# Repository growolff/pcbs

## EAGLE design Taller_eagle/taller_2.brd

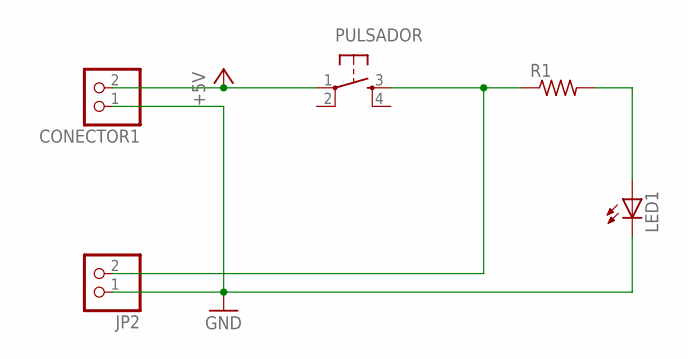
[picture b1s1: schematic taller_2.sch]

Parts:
CONECTOR1: PINHD-1X2/90; 1X02/90
JP2: PINHD-1X2/90; 1X02/90
LED1: LED5MM
PULSADOR: TAC_SWITCHPTH; TACTILE-PTH
R1: R-US_0207/12; 0207/12

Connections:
+5V: CONECTOR1.2, PULSADOR.1
GND: CONECTOR1.1, JP2.1, LED1.K (C)
unnamed: LED1.A, R1.2
unnamed: JP2.2, PULSADOR.3, R1.1

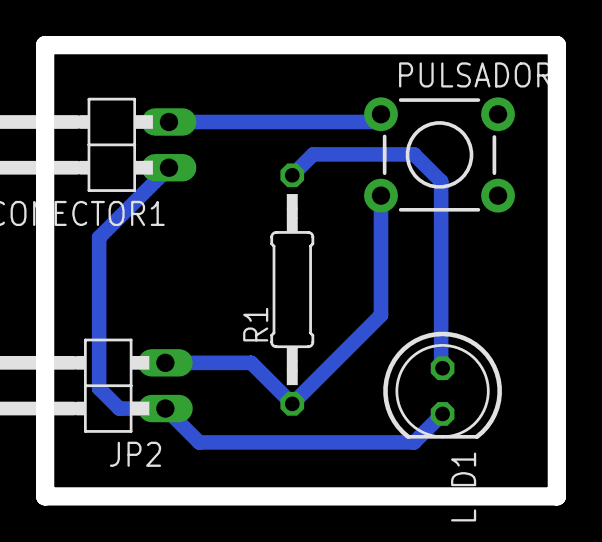
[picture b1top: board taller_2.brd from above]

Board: 2 copper layers, 28.4 x 25.1 mm, 5 parts (0 on the bottom side), 4 nets.

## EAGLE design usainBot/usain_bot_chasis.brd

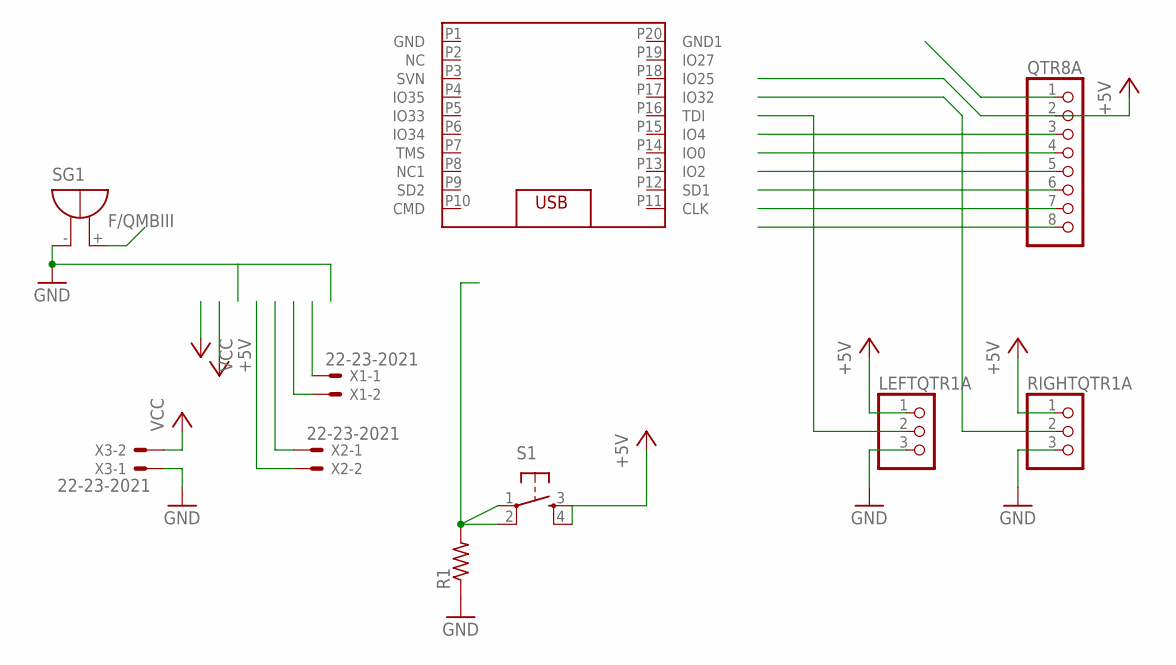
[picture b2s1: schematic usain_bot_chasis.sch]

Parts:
LEFTQTR1A: PINHD-1X3; 1X03
QTR8A: PINHD-1X8BIG; 1X08-BIG
R1: R-US_0207/7; 0207/7
RIGHTQTR1A: PINHD-1X3; 1X03
S1: TAC_SWITCHPTH; TACTILE-PTH
SG1: F/QMBIII
U$1: ESP32_MINI_KIT
X1, X2, X3: 22-23-2021

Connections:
+5V: LEFTQTR1A.1, QTR8A.2, RIGHTQTR1A.1, S1.3, S1.4
GND: LEFTQTR1A.3, R1.1, RIGHTQTR1A.3, SG1.- (+), X3.1
unnamed: R1.2, S1.1, S1.2
VCC: X3.2

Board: 2 copper layers, 10 parts (0 on the bottom side), 3 nets, no tracks yet.

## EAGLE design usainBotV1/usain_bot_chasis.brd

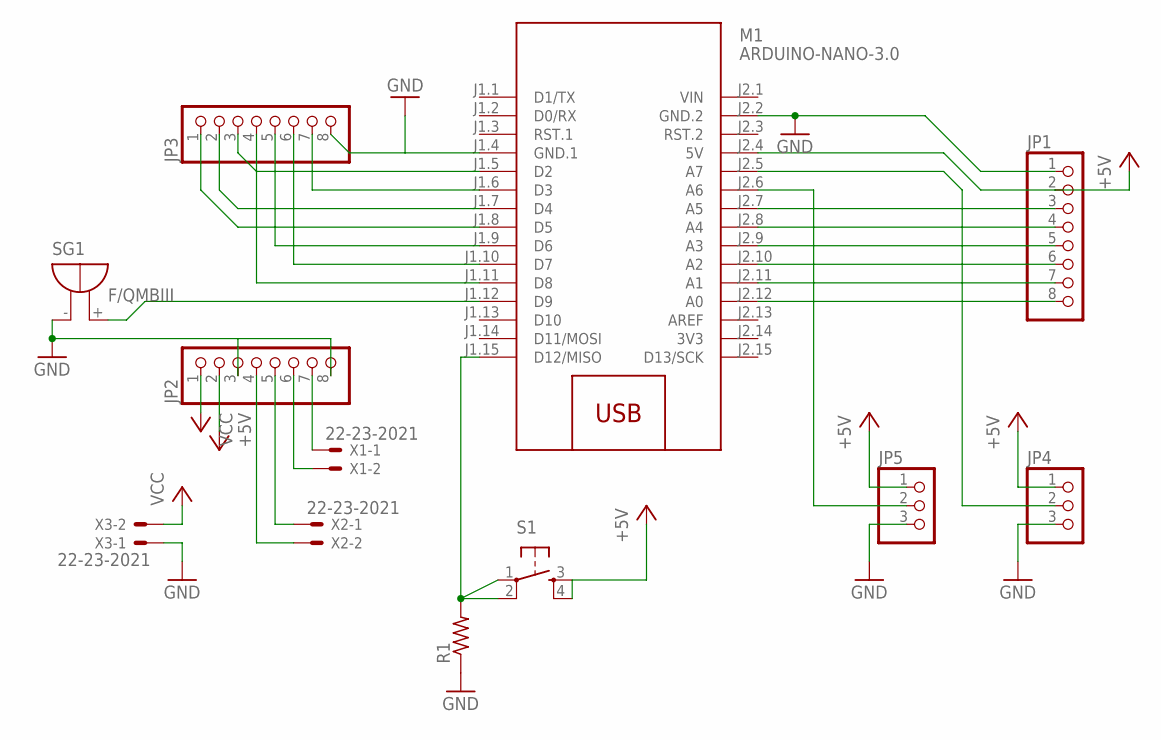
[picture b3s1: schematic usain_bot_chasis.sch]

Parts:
JP1, JP2, JP3: PINHD-1X8BIG; 1X08-BIG
JP4, JP5: PINHD-1X3; 1X03
M1: ARDUINO-NANO-3.0
R1: R-US_0207/7; 0207/7
S1: TAC_SWITCHPTH; TACTILE-PTH
SG1: F/QMBIII
X1, X2, X3: 22-23-2021

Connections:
3V3: M1.J2.14 (3V3)
+5V: JP1.2, JP2.2, JP4.1, JP5.1, M1.J2.4 (5V), S1.3, S1.4
GND: JP1.1, JP2.3, JP2.8, JP3.8, JP4.3, JP5.3, M1.J1.4 (GND.1), M1.J2.2 (GND.2), R1.1, SG1.- (+), X3.1
unnamed: JP1.8, M1.J2.12 (A0)
unnamed: JP1.7, M1.J2.11 (A1)
unnamed: JP1.6, M1.J2.10 (A2)
unnamed: JP1.5, M1.J2.9 (A3)
unnamed: JP1.4, M1.J2.8 (A4)
unnamed: JP1.3, M1.J2.7 (A5)
unnamed: M1.J1.15 (D12/MISO), R1.2, S1.1, S1.2
unnamed: JP3.7, M1.J1.6 (D3)
unnamed: JP3.1, M1.J1.8 (D5)
unnamed: JP3.2, M1.J1.7 (D4)
unnamed: JP3.3, M1.J1.5 (D2)
unnamed: JP3.5, M1.J1.9 (D6)
unnamed: JP3.6, M1.J1.10 (D7)
unnamed: JP3.4, M1.J1.11 (D8)
unnamed: JP2.4, X2.2
unnamed: JP2.5, X2.1
unnamed: JP2.6, X1.2
unnamed: JP2.7, X1.1
unnamed: M1.J1.12 (D9), SG1.+ (-)
unnamed: JP5.2, M1.J2.6 (A6)
unnamed: JP4.2, M1.J2.5 (A7)
VCC: JP2.1, X3.2
VIN: M1.J2.1 (VIN)

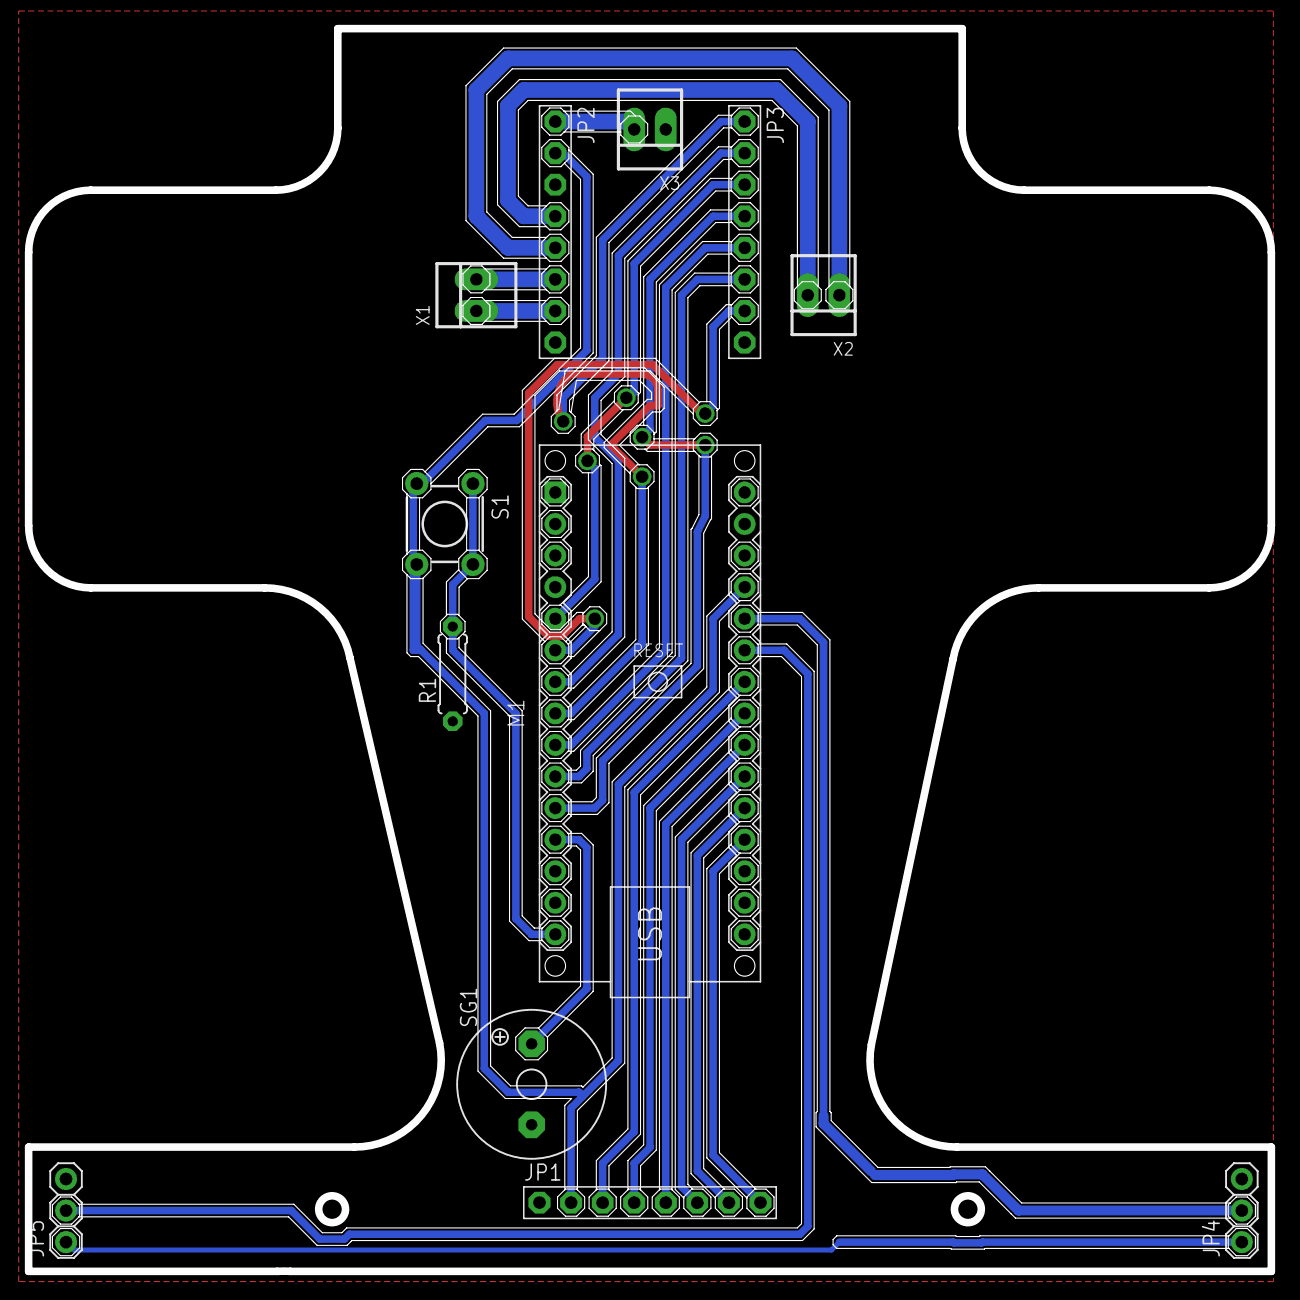
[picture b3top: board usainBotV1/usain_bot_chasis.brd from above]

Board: 2 copper layers, 100.0 x 100.0 mm, 12 parts (0 on the bottom side), 24 nets.

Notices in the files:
parts and their libraries:
SparkFun-Retired: Licensing:Creative Commons ShareAlike 4.0 International - https://creativecommons.org/licenses/by-sa/4.0
diy-modules: Released under the Creative Commons Attribution 4.0 International License: http://creativecommons.org/licenses/by/4.0
